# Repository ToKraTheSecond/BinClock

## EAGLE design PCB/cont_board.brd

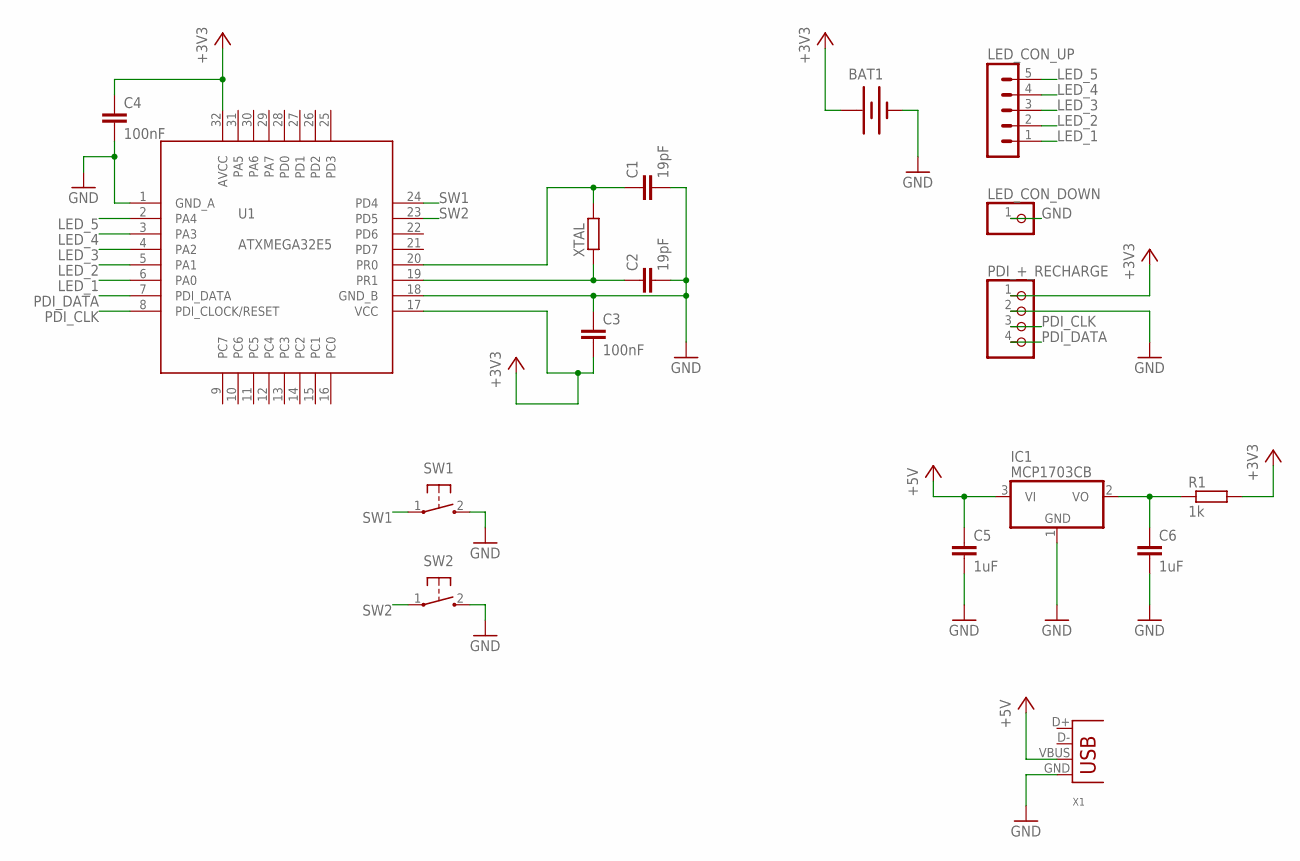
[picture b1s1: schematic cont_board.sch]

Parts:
BAT1: BATTERY12MM; BATTCON_12MM
C1, C2: 19pF; C0402
C3, C4: 100nF; C0402
C5, C6: 1uF; C0402
IC1: MCP1703CB; SOT23
LED_CON_DOWN: PINHD-1X1; 1X01
LED_CON_UP: MA05-1
PDI_+_RECHARGE: PINHD-1X4; 1X04
R1: 1k; R0402
SW1, SW2: TAC_SWITCHSMD; TACTILE-SWITCH-SMD
U1: ATXMEGA32E5; TQFP32-08
X1: USBMICRO-B; USB-MB-H
XTAL: R-EU_R0805; R0805

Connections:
+3V3: BAT1.PWR@1 (+), C3.2, C4.1, PDI_+_RECHARGE.1, R1.2, U1.17 (VCC), U1.32 (AVCC)
+5V: C5.1, IC1.3 (VI), X1.VBUS
GND: BAT1.GND (-), C1.2, C2.2, C3.1, C4.2, C5.2, C6.2, IC1.1 (GND), LED_CON_DOWN.1, PDI_+_RECHARGE.2, SW1.2 (3), SW2.2 (3), U1.1 (GND_A), U1.18 (GND_B), X1.GND
LED_1: LED_CON_UP.1, U1.6 (PA0)
LED_2: LED_CON_UP.2, U1.5 (PA1)
LED_3: LED_CON_UP.3, U1.4 (PA2)
LED_4: LED_CON_UP.4, U1.3 (PA3)
LED_5: LED_CON_UP.5, U1.2 (PA4)
unnamed: C1.1, U1.20 (PR0), XTAL.2
unnamed: C2.1, U1.19 (PR1), XTAL.1
unnamed: C6.1, IC1.2 (VO), R1.1
PDI_CLK: PDI_+_RECHARGE.3, U1.8 (PDI_CLOCK/RESET)
PDI_DATA: PDI_+_RECHARGE.4, U1.7 (PDI_DATA)
SW1: SW1.1, U1.24 (PD4)
SW2: SW2.1, U1.23 (PD5)

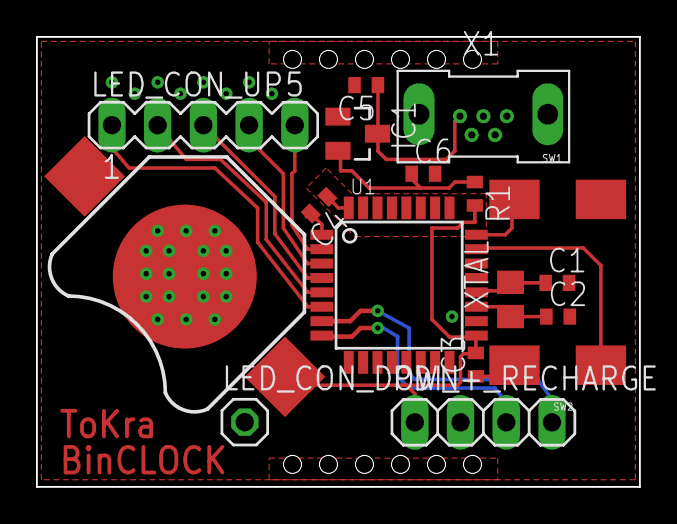
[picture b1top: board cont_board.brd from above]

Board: 2 copper layers, 33.5 x 25.0 mm, 17 parts (0 on the bottom side), 15 nets.

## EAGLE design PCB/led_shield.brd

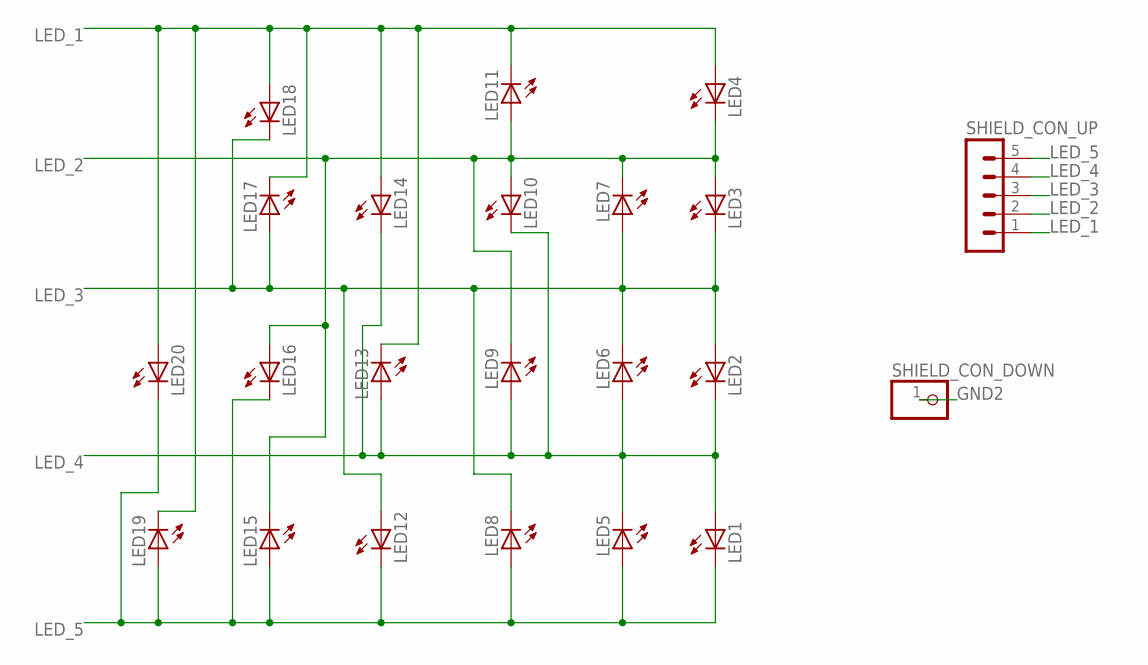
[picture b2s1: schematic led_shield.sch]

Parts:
LED1, LED2, LED3, LED4, LED5, LED6, LED7, LED8, LED9, LED10, LED11, LED12, LED13, LED14, LED15, LED16, LED17, LED18, LED19, LED20: LEDCHIP-LED0603; CHIP-LED0603
SHIELD_CON_DOWN: PINHD-1X1; 1X01
SHIELD_CON_UP: MA05-1

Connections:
GND2: SHIELD_CON_DOWN.1
LED_1: LED4.A, LED11.C, LED13.C, LED14.A, LED17.C, LED18.A, LED19.C, LED20.A, SHIELD_CON_UP.1
LED_2: LED3.A, LED4.C, LED7.C, LED9.C, LED10.A, LED11.A, LED15.C, LED16.A, SHIELD_CON_UP.2
LED_3: LED2.A, LED3.C, LED6.C, LED7.A, LED8.C, LED12.A, LED17.A, LED18.C, SHIELD_CON_UP.3
LED_4: LED1.A, LED2.C, LED5.C, LED6.A, LED9.A, LED10.C, LED13.A, LED14.C, SHIELD_CON_UP.4
LED_5: LED1.C, LED5.A, LED8.A, LED12.C, LED15.A, LED16.C, LED19.A, LED20.C, SHIELD_CON_UP.5

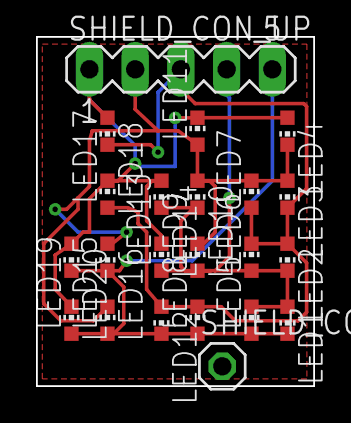
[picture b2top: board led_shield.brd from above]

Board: 2 copper layers, 15.4 x 19.4 mm, 22 parts (0 on the bottom side), 5 nets.

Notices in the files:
parts and their libraries:
SparkFun-Electromechanical: Licensing: Creative Commons ShareAlike 4.0 International - https://creativecommons.org/licenses/by-sa/4.0
